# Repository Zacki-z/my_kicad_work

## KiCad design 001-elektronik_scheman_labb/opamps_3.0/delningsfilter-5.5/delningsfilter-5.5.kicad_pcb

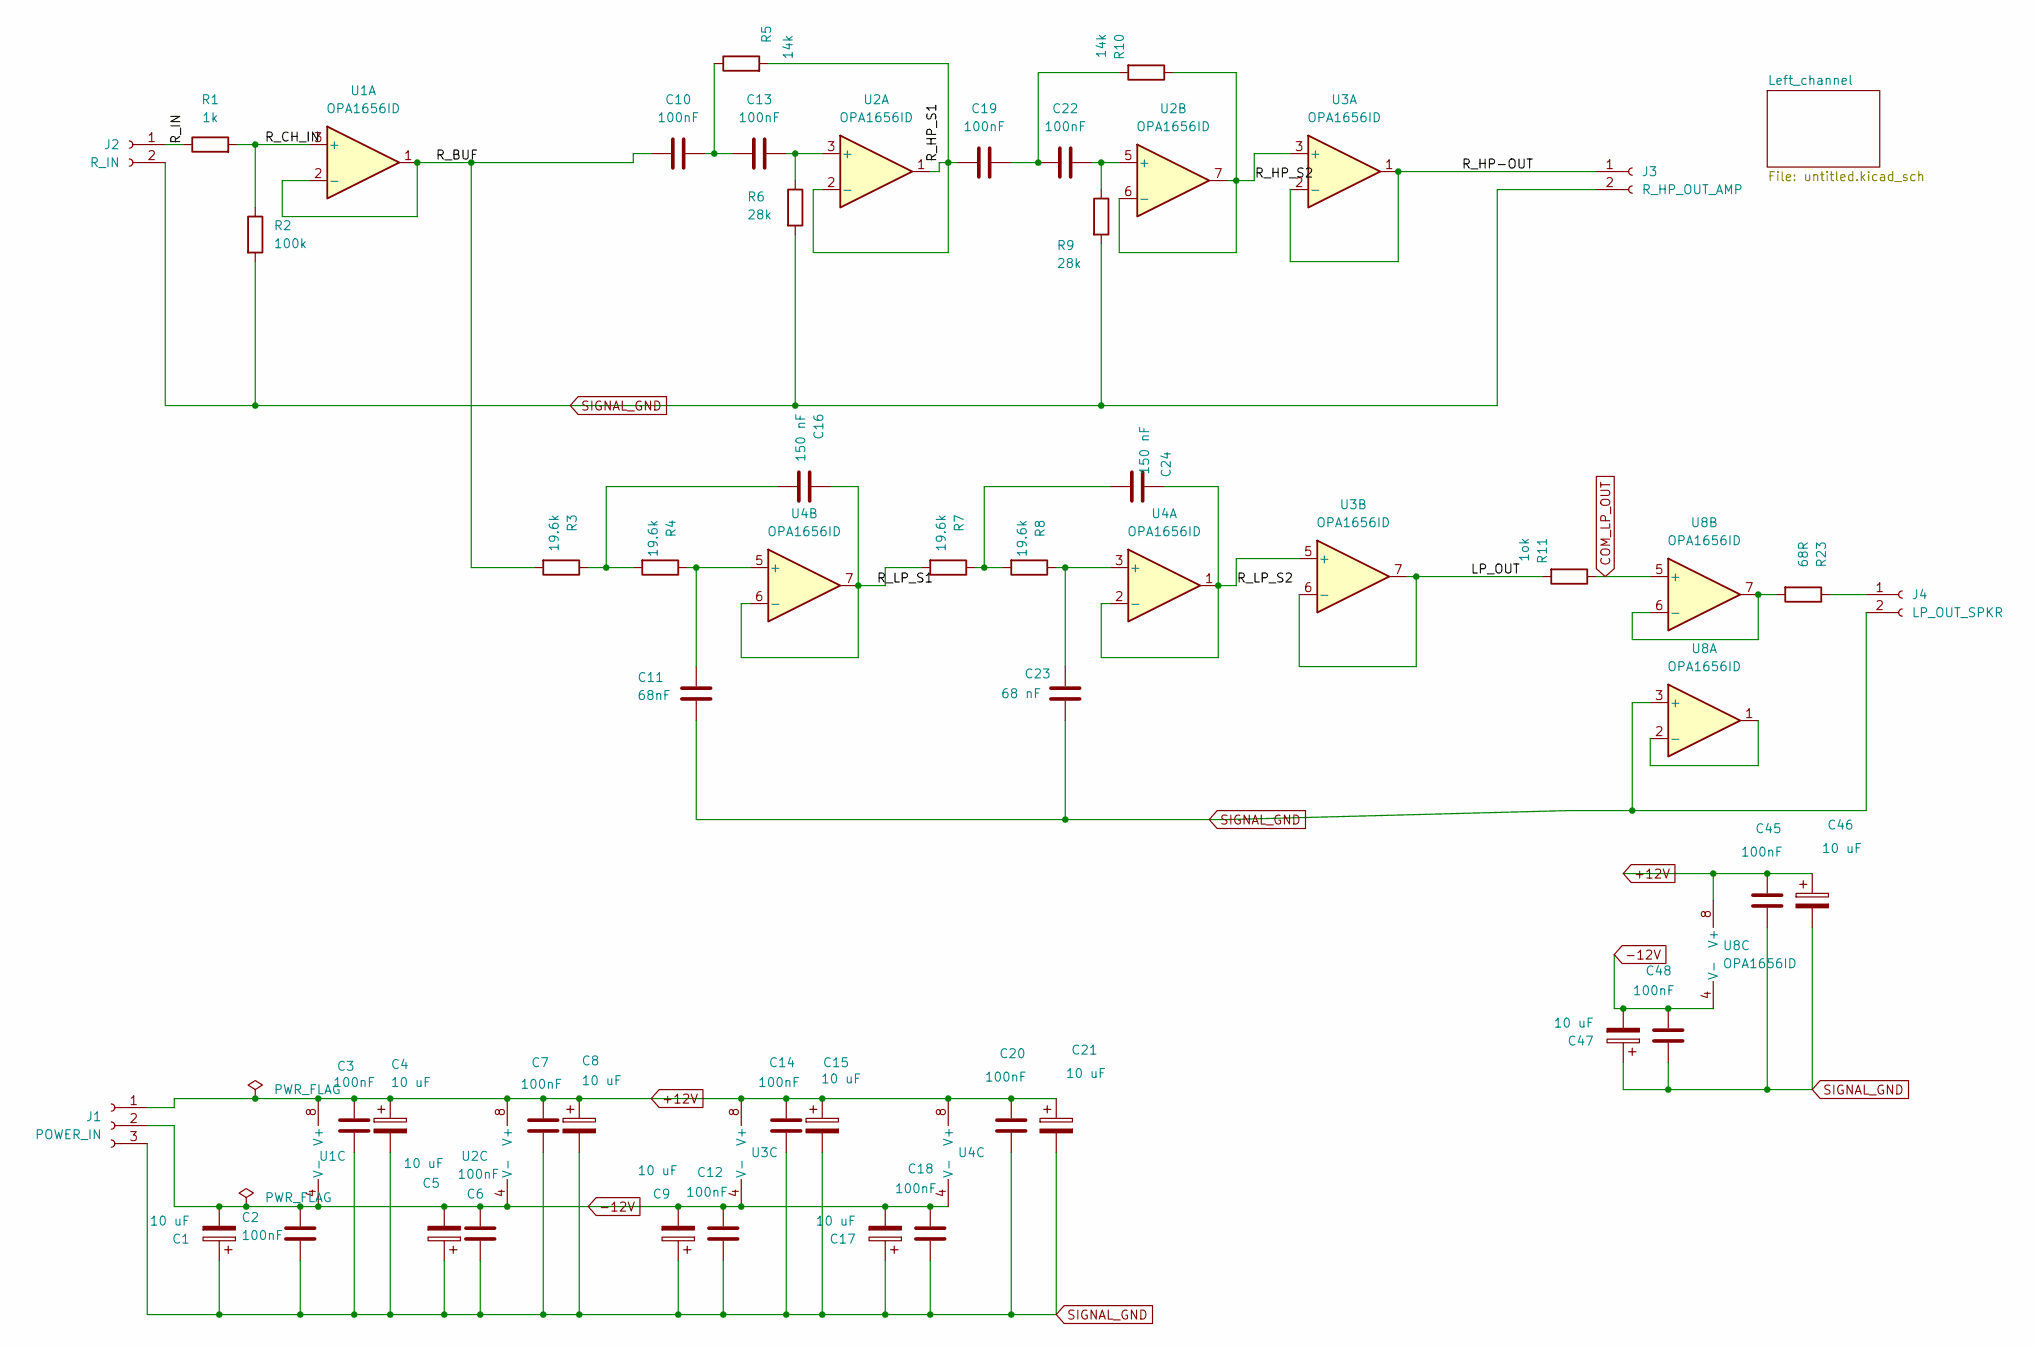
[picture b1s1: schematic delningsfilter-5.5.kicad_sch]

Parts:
C1, C4, C5, C8, C9, C15, C17, C21, C46, C47: 10 uF; CP_Radial_D5.0mm_P2.50mm
C2, C3, C6, C7, C12, C14, C18, C20, C45, C48: 100nF; C_Disc_D3.8mm_W2.6mm_P2.50mm
C10, C13, C19, C22: 100nF; C_Rect_L7.2mm_W2.5mm_P5.00mm_FKS2_FKP2_MKS2_MKP2
C11: 68nF; C_Rect_L7.2mm_W2.5mm_P5.00mm_FKS2_FKP2_MKS2_MKP2
C16, C24: 150 nF; C_Rect_L7.2mm_W2.5mm_P5.00mm_FKS2_FKP2_MKS2_MKP2
C23: 68 nF; C_Rect_L7.2mm_W2.5mm_P5.00mm_FKS2_FKP2_MKS2_MKP2
J1: POWER_IN; PinHeader_1x03_P2.54mm_Vertical
J2: R_IN; PinHeader_1x02_P2.54mm_Vertical
J3: R_HP_OUT_AMP; PinHeader_1x02_P2.54mm_Vertical
J4: LP_OUT_SPKR; PinHeader_1x02_P2.54mm_Vertical
R1: 1k; R_Axial_DIN0207_L6.3mm_D2.5mm_P7.62mm_Horizontal
R2: 100k; R_Axial_DIN0207_L6.3mm_D2.5mm_P7.62mm_Horizontal
R3, R4, R7, R8: 19.6k; R_Axial_DIN0207_L6.3mm_D2.5mm_P7.62mm_Horizontal
R5, R10: 14k; R_Axial_DIN0207_L6.3mm_D2.5mm_P7.62mm_Horizontal
R6, R9: 28k; R_Axial_DIN0207_L6.3mm_D2.5mm_P7.62mm_Horizontal
R11: 1ok; R_Axial_DIN0207_L6.3mm_D2.5mm_P7.62mm_Horizontal
R23: 68R; R_Axial_DIN0207_L6.3mm_D2.5mm_P7.62mm_Horizontal
U1, U2, U3, U4, U8: OPA1656ID; DIP-8_W7.62mm

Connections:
+12V: C3.1, C4.1, C7.1, C8.1, C14.1, C15.1, C20.1, C21.1, C45.1, C46.1, J1.1, U1.8 (V+), U2.8 (V+), U3.8 (V+), U4.8 (V+), U8.8 (V+); also elsewhere on the board
-12V: C1.2, C2.1, C5.2, C6.1, C9.2, C12.1, C17.2, C18.1, C47.2, C48.1, J1.2, U1.4 (V-), U2.4 (V-), U3.4 (V-), U4.4 (V-), U8.4 (V-); also elsewhere on the board
/LP_OUT: R11.2, U3.6 (-), U3.7
/R_BUF: C10.2, R3.2, U1.1, U1.2 (-)
/R_CH_IN: R1.2, R2.1, U1.3 (+)
/R_HP-OUT: J3.1, U3.1, U3.2 (-); also elsewhere on the board
/R_HP_S1: C19.2, R5.2, U2.1, U2.2 (-)
/R_HP_S2: R10.1, U2.6 (-), U2.7, U3.3 (+)
/R_IN: J2.1, R1.1; also elsewhere on the board
/R_LP_S1: C16.1, R7.2, U4.6 (-), U4.7
/R_LP_S2: C24.2, U3.5 (+), U4.1, U4.2 (-)
unnamed: C10.1, C13.2, R5.1
unnamed: C16.2, R3.1, R4.2
unnamed: C19.1, C22.2, R10.2
unnamed: C24.1, R7.1, R8.2
unnamed: C13.1, R6.1, U2.3 (+)
unnamed: C22.1, R9.1, U2.5 (+)
unnamed: C23.1, R8.1, U4.3 (+)
unnamed: C11.1, R4.1, U4.5 (+)
unnamed: U8.1, U8.2 (-)
unnamed: R23.2, U8.6 (-), U8.7
SIGNAL_GND: C1.1, C2.2, C3.2, C4.2, C5.1, C6.2, C7.2, C8.2, C9.1, C11.2, C12.2, C14.2, C15.2, C17.1, C18.2, C20.2, C21.2, C23.2, C45.2, C46.2, C47.1, C48.2, J1.3, J2.2, J3.2, J4.2, R2.2, R6.2, R9.2, U8.3 (+); also elsewhere on the board

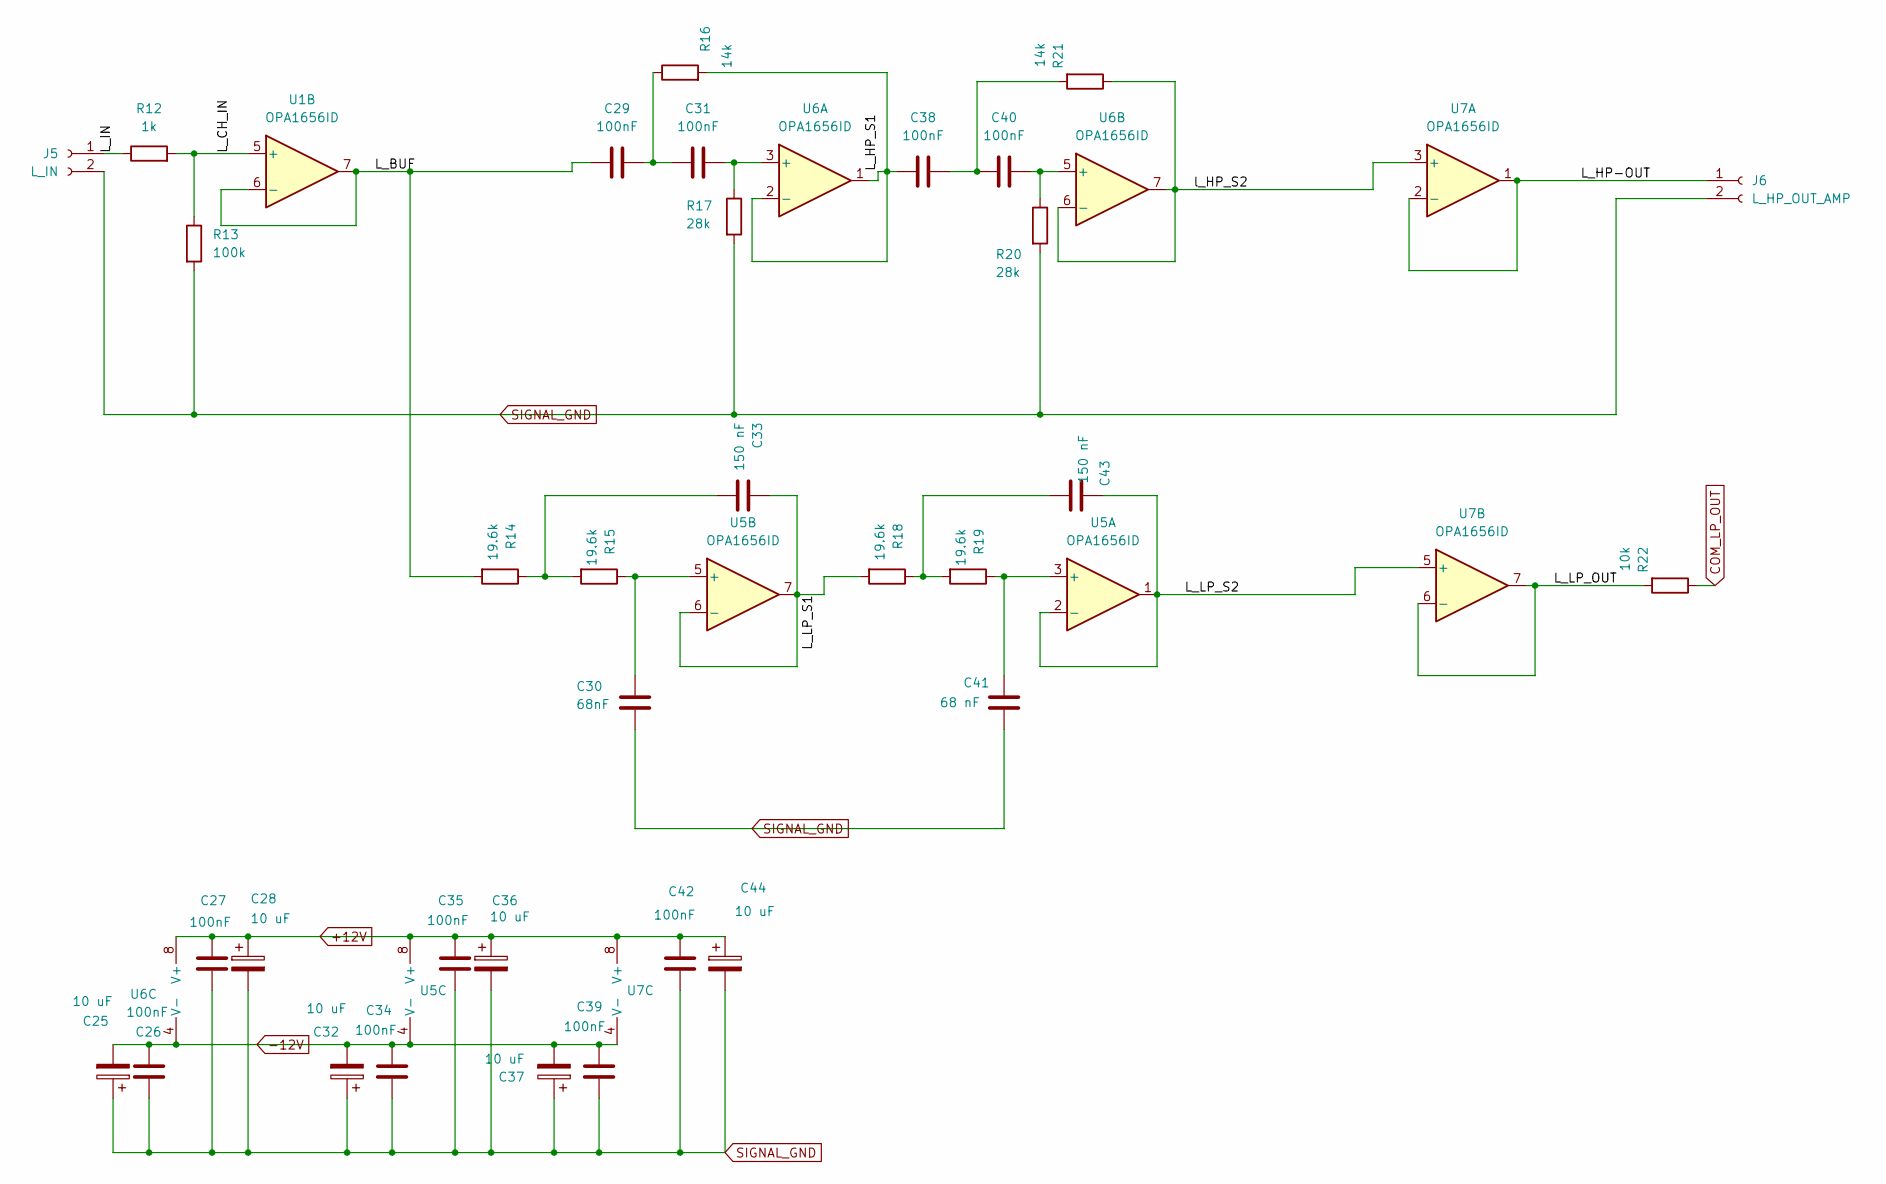
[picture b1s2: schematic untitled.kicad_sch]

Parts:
C25, C28, C32, C44: 10 uF; CP_Radial_D5.0mm_P2.50mm
C26, C27, C34, C35, C39, C42: 100nF; C_Disc_D3.8mm_W2.6mm_P2.50mm
C29, C31, C38, C40: 100nF; C_Rect_L7.2mm_W2.5mm_P5.00mm_FKS2_FKP2_MKS2_MKP2
C30: 68nF; C_Rect_L7.0mm_W6.5mm_P5.00mm
C33, C43: 150 nF; C_Rect_L7.2mm_W2.5mm_P5.00mm_FKS2_FKP2_MKS2_MKP2
C36, C37: 10 uF; CP_Radial_D5.0mm_P2.00mm
C41: 68 nF; C_Rect_L7.2mm_W2.5mm_P5.00mm_FKS2_FKP2_MKS2_MKP2
J5: L_IN; PinHeader_1x02_P2.54mm_Vertical
J6: L_HP_OUT_AMP; PinHeader_1x02_P2.54mm_Vertical
R12: 1k; R_Axial_DIN0207_L6.3mm_D2.5mm_P7.62mm_Horizontal
R13: 100k; R_Axial_DIN0207_L6.3mm_D2.5mm_P7.62mm_Horizontal
R14, R15, R18, R19: 19.6k; R_Axial_DIN0207_L6.3mm_D2.5mm_P7.62mm_Horizontal
R16, R21: 14k; R_Axial_DIN0207_L6.3mm_D2.5mm_P7.62mm_Horizontal
R17, R20: 28k; R_Axial_DIN0207_L6.3mm_D2.5mm_P7.62mm_Horizontal
R22: 10k; R_Axial_DIN0207_L6.3mm_D2.5mm_P7.62mm_Horizontal
U1, U5, U6, U7: OPA1656ID; DIP-8_W7.62mm

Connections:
+12V: C27.1, C28.1, C35.1, C36.1, C42.1, C44.1, U5.8 (V+), U6.8 (V+), U7.8 (V+); also elsewhere on the board
-12V: C25.2, C26.1, C32.2, C34.1, C37.2, C39.1, U5.4 (V-), U6.4 (V-), U7.4 (V-); also elsewhere on the board
/Left_channel/L_BUF: C29.2, R14.2, U1.6 (-), U1.7
/Left_channel/L_CH_IN: R12.2, R13.1, U1.5 (+)
/Left_channel/L_HP-OUT: J6.1, U7.1, U7.2 (-); also elsewhere on the board
/Left_channel/L_HP_S1: C38.2, R16.2, U6.1, U6.2 (-)
/Left_channel/L_IN: J5.1, R12.1; also elsewhere on the board
/Left_channel/L_LP_OUT: R22.2, U7.6 (-), U7.7
/Left_channel/L_LP_S1: C33.1, R18.2, U5.6 (-), U5.7
/Left_channel/L_LP_S2: C43.2, U5.1, U5.2 (-), U7.5 (+)
/Left_channel/l_HP_S2: R21.1, U6.6 (-), U6.7, U7.3 (+)
unnamed: C29.1, C31.2, R16.1
unnamed: C33.2, R14.1, R15.2
unnamed: C38.1, C40.2, R21.2
unnamed: C43.1, R18.1, R19.2
unnamed: C41.1, R19.1, U5.3 (+)
unnamed: C30.1, R15.1, U5.5 (+)
unnamed: C31.1, R17.1, U6.3 (+)
unnamed: C40.1, R20.1, U6.5 (+)
SIGNAL_GND: C25.1, C26.2, C27.2, C28.2, C30.2, C32.1, C34.2, C35.2, C36.2, C37.1, C39.2, C41.2, C42.2, C44.2, J5.2, J6.2, R13.2, R17.2, R20.2; also elsewhere on the board

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
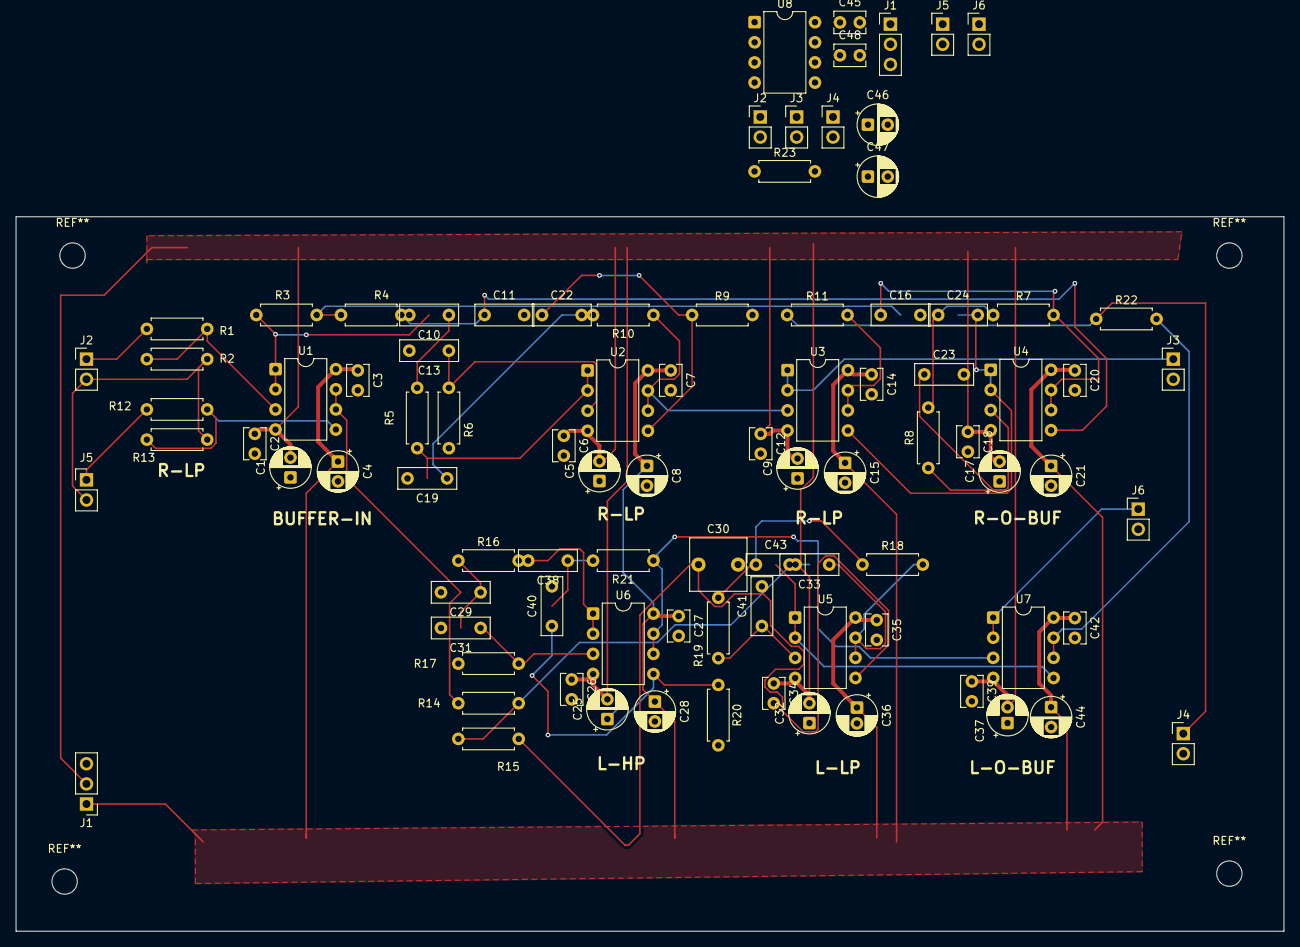
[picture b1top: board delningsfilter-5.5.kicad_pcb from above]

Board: 2 copper layers, 160.0 x 90.2 mm, 91 parts (0 on the bottom side), 41 nets.

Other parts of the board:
J1#2: POWER; PinHeader_1x03_P2.54mm_Vertical
J2#2: R_IN; PinHeader_1x02_P2.54mm_Vertical
J3#2: Right_out; PinHeader_1x02_P2.54mm_Vertical
J4#2: LP_OUT_SPKR; PinHeader_1x02_P2.54mm_Vertical
J5#2: LEFT_in; PinHeader_1x02_P2.54mm_Vertical
J6#2: LEFT_OUT; PinHeader_1x02_P2.54mm_Vertical

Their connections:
+12V: J1#2.1; also elsewhere on the board
-12V: J1#2.2; also elsewhere on the board
/Left_channel/L_HP-OUT: J6#2.1; also elsewhere on the board
/Left_channel/L_IN: J5#2.1; also elsewhere on the board
/R_HP-OUT: J3#2.1; also elsewhere on the board
/R_IN: J2#2.1; also elsewhere on the board
SIGNAL_GND: J1#2.3, J2#2.2, J3#2.2, J4#2.2, J5#2.2, J6#2.2; also elsewhere on the board

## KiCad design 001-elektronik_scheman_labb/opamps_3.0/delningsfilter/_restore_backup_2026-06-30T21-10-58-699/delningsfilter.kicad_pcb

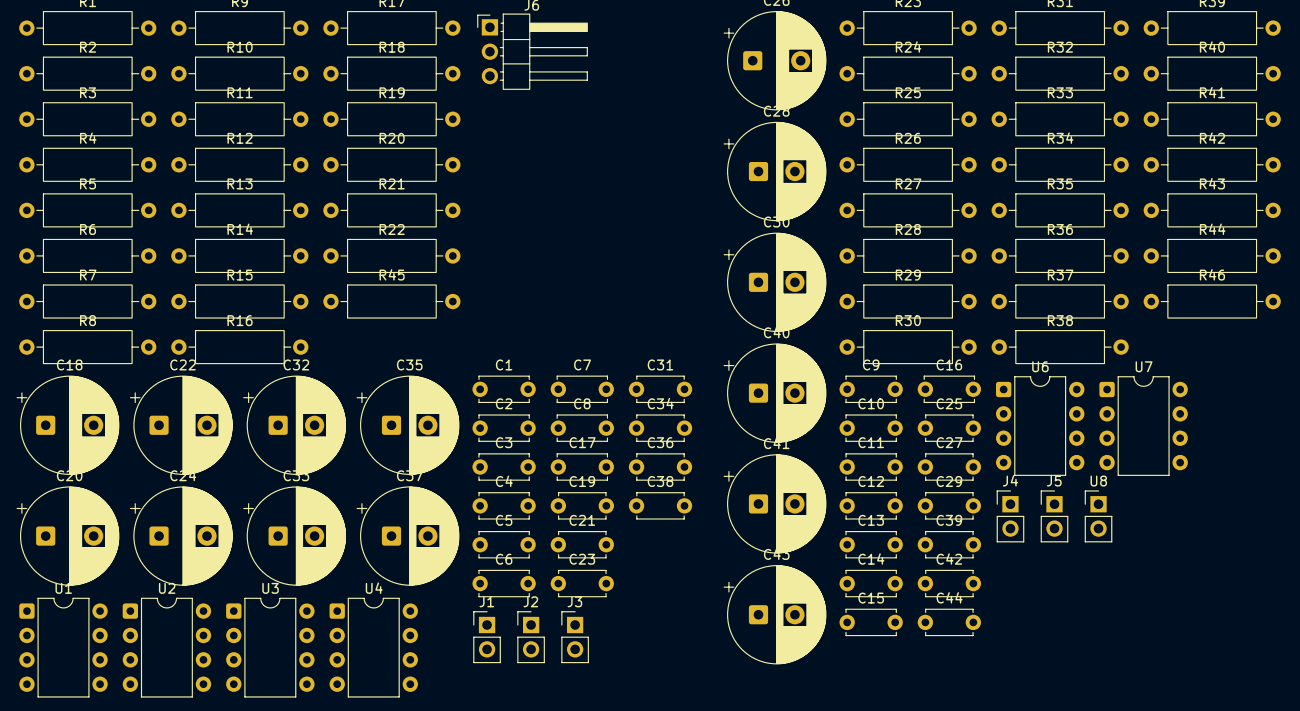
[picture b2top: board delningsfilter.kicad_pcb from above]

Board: 2 copper layers, 103 parts (0 on the bottom side), 49 nets, no tracks yet.

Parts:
C1, C2, C3, C4, C5, C6, C7, C8, C9, C10, C11, C12, C13, C14, C15, C16, C17: 100nF; C_Disc_D5.0mm_W2.5mm_P5.00mm
C18, C20, C22, C24, C26: 10 uF; CP_Radial_D10.0mm_P5.00mm
C19, C21, C23, C25, C27, C29, C31, C34, C36, C38, C39, C42, C44: 100nF; C_Disc_D4.7mm_W2.5mm_P5.00mm
C28, C30, C32, C33, C35, C37, C40, C41, C43: 10 uF; CP_Radial_D10.0mm_P3.80mm
J1, J2, J3, J4, J5: Conn_01x02_Pin; PinHeader_1x02_P2.54mm_Vertical
J6: Conn_01x03_Pin; PinHeader_1x03_P2.54mm_Horizontal
R1, R23: 1k; R_Axial_DIN0309_L9.0mm_D3.2mm_P12.70mm_Horizontal
R2, R24: 100k; R_Axial_DIN0309_L9.0mm_D3.2mm_P12.70mm_Horizontal
R3, R6, R11, R12, R13, R14, R19, R20, R25, R26, R27, R29, R33, R34, R35, R36: 19.9k; R_Axial_DIN0309_L9.0mm_D3.2mm_P12.70mm_Horizontal
R4, R8, R16, R18, R31, R32, R39, R40: 5.9k; R_Axial_DIN0309_L9.0mm_D3.2mm_P12.70mm_Horizontal
R5, R7, R10, R15, R17, R22, R28, R30, R37, R38, R43, R44, R45, R46: 10k; R_Axial_DIN0309_L9.0mm_D3.2mm_P12.70mm_Horizontal
R9, R21, R41, R42: 15k; R_Axial_DIN0309_L9.0mm_D3.2mm_P12.70mm_Horizontal
U1, U2, U3, U4, U6, U7: OPA1656ID; DIP-8_W7.62mm
U8: OPA1656ID; PinHeader_1x02_P2.54mm_Vertical

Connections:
+12V: C17.1, C17.2, C18.1, C18.2, C19.1, C19.2, C20.1, C20.2, C21.1, C21.2, C22.1, C22.2, C23.1, C23.2, C24.1, C24.2, C25.1, C25.2, C26.1, C26.2, C27.1, C27.2, C28.1, C28.2, C29.1, C29.2, C30.1, C30.2, J6.2, U1.8 (V+), U2.8 (V+), U3.8 (V+), U4.8 (V+), U6.8 (V+), U7.8 (V+)
-12V: C31.1, C31.2, C32.1, C32.2, C33.1, C33.2, C34.1, C34.2, C35.1, C35.2, C36.1, C36.2, C37.1, C37.2, C38.1, C38.2, C39.1, C39.2, C40.1, C40.2, C41.1, C41.2, C42.1, C42.2, C43.1, C43.2, C44.1, C44.2, J6.3, U1.4 (V-), U2.4 (V-), U3.4 (V-), U4.4 (V-), U6.4 (V-), U7.4 (V-)
/RIGHT_CH_IN: J1.1, R1.1
/RIGHT_HP-OUT: J2.1, U3.1, U3.2 (-)
/RIGHT_LP_OUT: R45.1, U3.6 (-), U3.7
/left channel/LEFT_CH_IN: J4.1, R23.1
/left channel/LEFT_HP-OUT: J5.1, U8.1, U8.2 (-_2)
LP_OUT: J3.1, R45.2, R46.2
unnamed: C1.1, C2.2, R3.1
unnamed: C3.1, C4.2, R6.1
unnamed: C3.2, R4.1, U2.1
unnamed: C5.1, R13.1, R14.2
unnamed: C7.2, R19.1, R20.2
unnamed: C9.1, R25.1, R26.2
unnamed: C10.1, C12.2, R27.1
unnamed: C13.1, C15.2, R35.1
unnamed: C13.2, R32.1, U7.1
unnamed: C14.2, R33.1, R34.2
unnamed: R8.1, R9.1, U2.7
unnamed: R16.1, R19.2, U4.7
unnamed: R18.1, R21.1, U4.1
unnamed: R31.1, R33.2, U6.7
unnamed: R39.1, R42.1, U6.1
unnamed: R40.1, R41.1, U7.7
unnamed: R1.2, R2.1, U1.3 (+)
unnamed: C1.2, R13.2, U1.1, U1.2 (-)
unnamed: R23.2, R24.1, U1.5 (+)
unnamed: C10.2, R25.2, U1.6 (-), U1.7
unnamed: C2.1, R11.1, U2.3 (+)
unnamed: R4.2, R5.1, U2.2 (-)
unnamed: C4.1, R12.1, U2.5 (+)
unnamed: R7.1, R8.2, U2.6 (-)
unnamed: R9.2, R10.1, U3.3 (+)
unnamed: R21.2, R22.1, U3.5 (+)
unnamed: C8.1, R20.1, U4.3 (+)
unnamed: R17.1, R18.2, U4.2 (-)
unnamed: C6.1, R14.1, U4.5 (+)
unnamed: R15.1, R16.2, U4.6 (-)
unnamed: C16.1, R34.1, U6.3 (+)
unnamed: R37.1, R39.2, U6.2 (-)
unnamed: C11.1, R26.1, U6.5 (+)
unnamed: R28.1, R31.2, U6.6 (-)
unnamed: C12.1, R29.1, U7.3 (+)
unnamed: R30.1, R32.2, U7.2 (-)
unnamed: C15.1, R36.1, U7.5 (+)
unnamed: R38.1, R40.2, U7.6 (-)
unnamed: R41.2, R43.1
unnamed: R42.2, R44.1
a-signal_gnd: C5.2, C6.2, C7.1, C8.2, C9.2, C11.2, C14.1, C16.2, J1.2, J2.2, J3.2, J4.2, J5.2, J6.1, R2.2, R3.2, R5.2, R6.2, R7.2, R10.2, R11.2, R12.2, R15.2, R17.2, R22.2, R24.2, R27.2, R28.2, R29.2, R30.2, R35.2, R36.2, R37.2, R38.2, R43.2, R44.2

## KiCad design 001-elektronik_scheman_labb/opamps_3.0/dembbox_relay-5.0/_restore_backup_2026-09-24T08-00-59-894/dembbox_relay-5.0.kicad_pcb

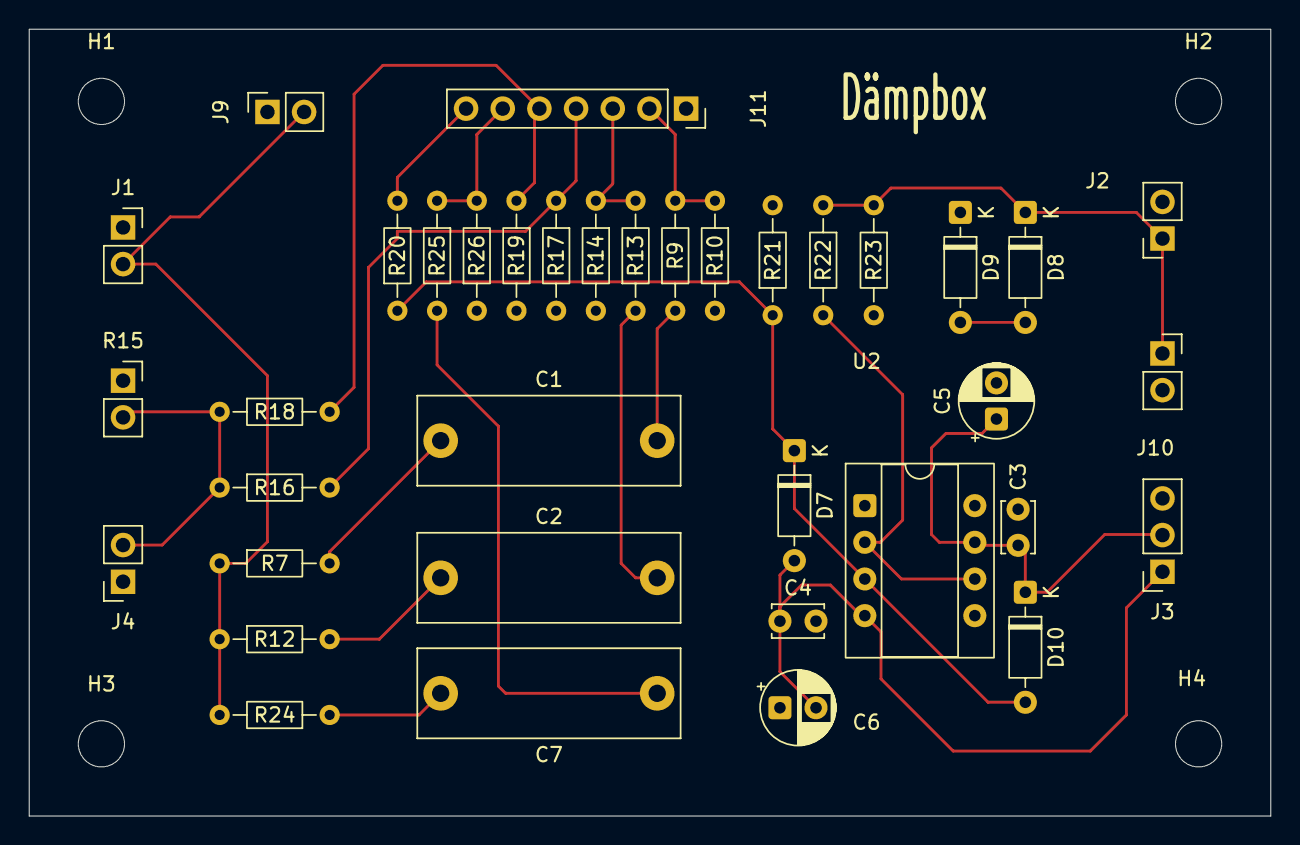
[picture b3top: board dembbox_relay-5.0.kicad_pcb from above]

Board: 2 copper layers, 86.0 x 54.5 mm, 41 parts (0 on the bottom side), 21 nets.

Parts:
C1, C2: 100 nF 630v; C_Rect_L18.0mm_W6.0mm_P15.00mm_FKS3_FKP3
C3, C4: 100 nF; C_Disc_D3.4mm_W2.1mm_P2.50mm
C5, C6: 10 uF; CP_Radial_D5.0mm_P2.50mm
C7: 100 nF 630V; C_Rect_L18.0mm_W6.0mm_P15.00mm_FKS3_FKP3
D7, D10: 1N4148; D_DO-35_SOD27_P7.62mm_Horizontal
D8, D9: BZX55C5V1; D_DO-35_SOD27_P7.62mm_Horizontal
H1, H2, H3, H4: MountingHole; MountingHole_3.2mm_M3
J1: Test_probe; PinSocket_1x02_P2.54mm_Vertical
J2: TO_Focusrite_input; PinSocket_1x02_P2.54mm_Vertical
J3: OP_AMP_PWR; PinSocket_1x03_P2.54mm_Vertical
J4: Speaker; PinSocket_1x02_P2.54mm_Vertical
J9, J10: Mätinstrument; PinSocket_1x02_P2.54mm_Vertical
J11: J_SW_SIGNAL; PinSocket_1x07_P2.54mm_Vertical
R7, R12, R21, R26: 1M; R_Axial_DIN0204_L3.6mm_D1.6mm_P7.62mm_Horizontal
R9, R13: 953k; R_Axial_DIN0204_L3.6mm_D1.6mm_P7.62mm_Horizontal
R10: 20K; R_Axial_DIN0204_L3.6mm_D1.6mm_P7.62mm_Horizontal
R14: 274k; R_Axial_DIN0204_L3.6mm_D1.6mm_P7.62mm_Horizontal
R15: 8 50W; PinSocket_1x02_P2.54mm_Vertical
R16, R23: 100k; R_Axial_DIN0204_L3.6mm_D1.6mm_P7.62mm_Horizontal
R17: 1k; R_Axial_DIN0204_L3.6mm_D1.6mm_P7.62mm_Horizontal
R18: 90,9k; R_Axial_DIN0204_L3.6mm_D1.6mm_P7.62mm_Horizontal
R19: 10k; R_Axial_DIN0204_L3.6mm_D1.6mm_P7.62mm_Horizontal
R20: 20k; R_Axial_DIN0204_L3.6mm_D1.6mm_P7.62mm_Horizontal
R22: 330R; R_Axial_DIN0204_L3.6mm_D1.6mm_P7.62mm_Horizontal
R24, R25: 10K; R_Axial_DIN0204_L3.6mm_D1.6mm_P7.62mm_Horizontal
U2: OPA134; CERDIP-8_W7.62mm_SideBrazed_Socket

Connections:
/INTPUT: J1.2, J9.2, R7.1, R12.1, R24.2
/INT_1_10: C2.1, R12.2
/INT_1_10_OUT: J11.3, R13.2, R14.1
/INT_1_100: C1.1, R7.2
/INT_1_100_OUT: J11.2, R9.2, R10.1
/LOW_1_1: C7.2, R24.1
/LOW_1_1_OUT: J11.6, R25.1, R26.2
/SPK_1_10_OUT: J11.5, R18.2, R19.1
/SPK_1_100: J4.2, R15.2, R16.1, R18.1
/SPK_1_100_OUT: J11.4, R16.2, R17.1
/sound-card/12V+: C3.1, C5.1, D10.1 (K), J3.2, U2.7 (V+)
/sound-card/12V-: C4.1, C6.2, D7.2 (A), J3.1, U2.4 (V-)
/sound-card/OP_AMP_OUT: R22.2, U2.2 (-), U2.6
/sound-card/audio_out: D8.1 (K), J2.1, J10.1, R22.1, R23.1
MEASURE_GND: C3.2, C4.2, C5.2, C6.1, D9.1 (K), J1.1, J2.2, J3.3, J4.1, J9.1, J10.2, R10.2, R14.2, R15.1, R17.2, R19.2, R21.2, R23.2, R26.1
MEASURE_SIGNAL: J11.7, R20.2
unnamed: C1.2, R9.1
unnamed: C2.2, R13.1
unnamed: C7.1, R25.2
unnamed: D8.2 (A), D9.2 (A)
unnamed: D7.1 (K), D10.2 (A), R20.1, R21.1, U2.3 (+)
